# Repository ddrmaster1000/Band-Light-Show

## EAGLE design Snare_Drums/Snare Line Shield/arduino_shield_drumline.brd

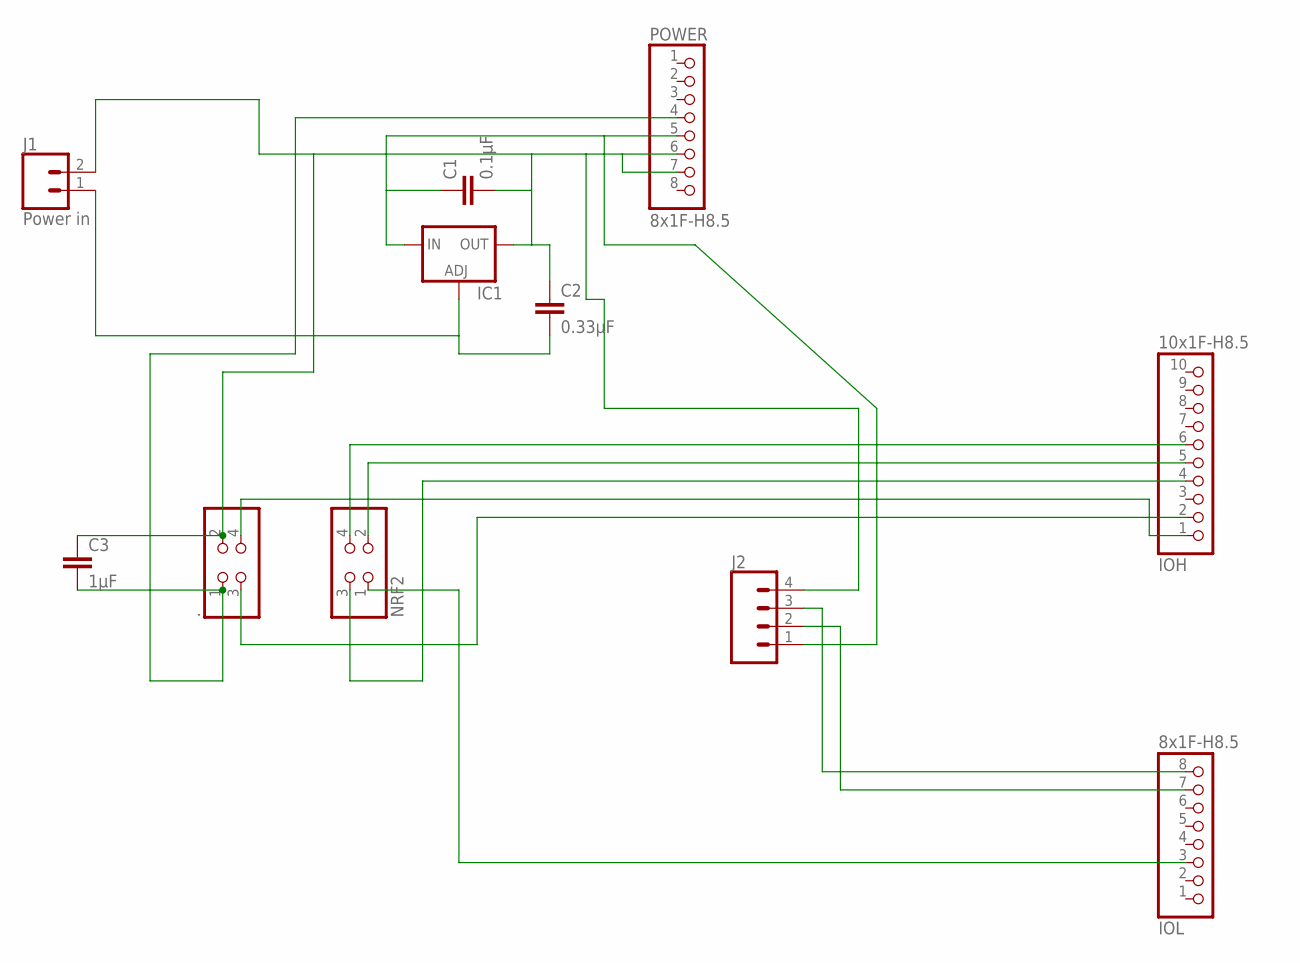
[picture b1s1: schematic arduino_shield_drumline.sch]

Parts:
.: PINHD-2X2; 2X02
C1: 0.1µF; 0805
C2: 0.33µF; 0805
C3: 1µF; 0805
IC1: LM138-TS; TO220S
IOH: 10x1F-H8.5; 1X10
IOL: 8x1F-H8.5; 1X08
J1: Power in; 1X02
J2: CONN_04; 1X04
NRF2: PINHD-2X2; 2X02
POWER: 8x1F-H8.5; 1X08

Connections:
GND: ..2, C1.2, C2.1, C3.1, IC1.2 (OUT), J1.2, J2.4, POWER.6, POWER.7
unnamed: ..1, C3.2, POWER.4
unnamed: IOH.5, NRF2.2
unnamed: ..4, IOH.1
unnamed: ..3, IOH.2
unnamed: IOH.6, NRF2.4
unnamed: IOL.3, NRF2.1
unnamed: IOH.4, NRF2.3
unnamed: C1.1, IC1.3 (IN), J2.1, POWER.5
unnamed: C2.2, IC1.1 (ADJ), J1.1
unnamed: IOL.8, J2.3
unnamed: IOL.7, J2.2

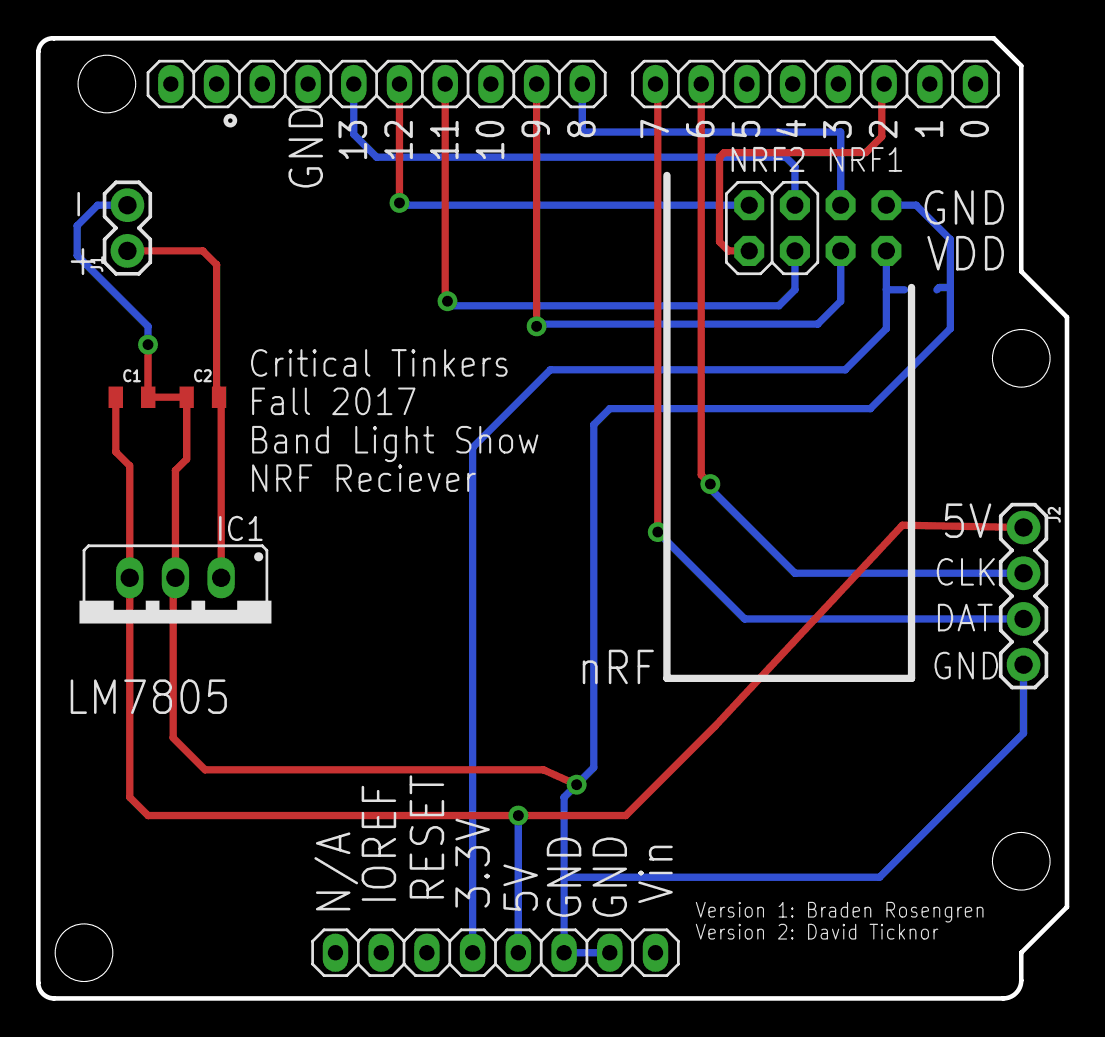
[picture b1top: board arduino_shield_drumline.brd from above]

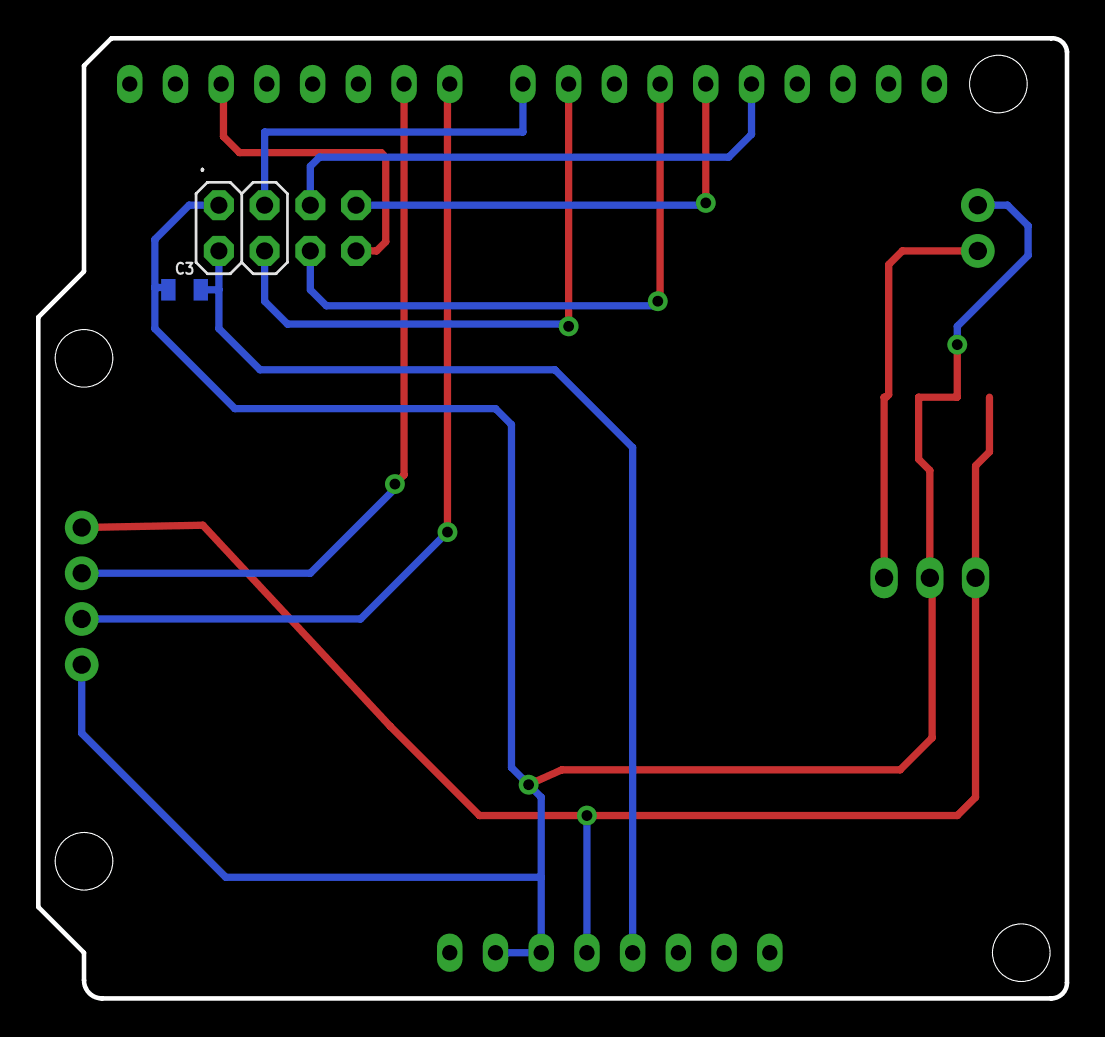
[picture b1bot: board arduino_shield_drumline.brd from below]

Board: 2 copper layers, 57.2 x 53.3 mm, 11 parts (2 on the bottom side), 12 nets.

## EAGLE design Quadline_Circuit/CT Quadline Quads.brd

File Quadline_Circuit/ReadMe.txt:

The Quadline was made such that it was the bassline diagram copied 4x with the GND and 12V connected accordingly. 
Thus there is no schematic, it will say there is an error but this is not an issue.
Developed on EAGLE 8.3.1

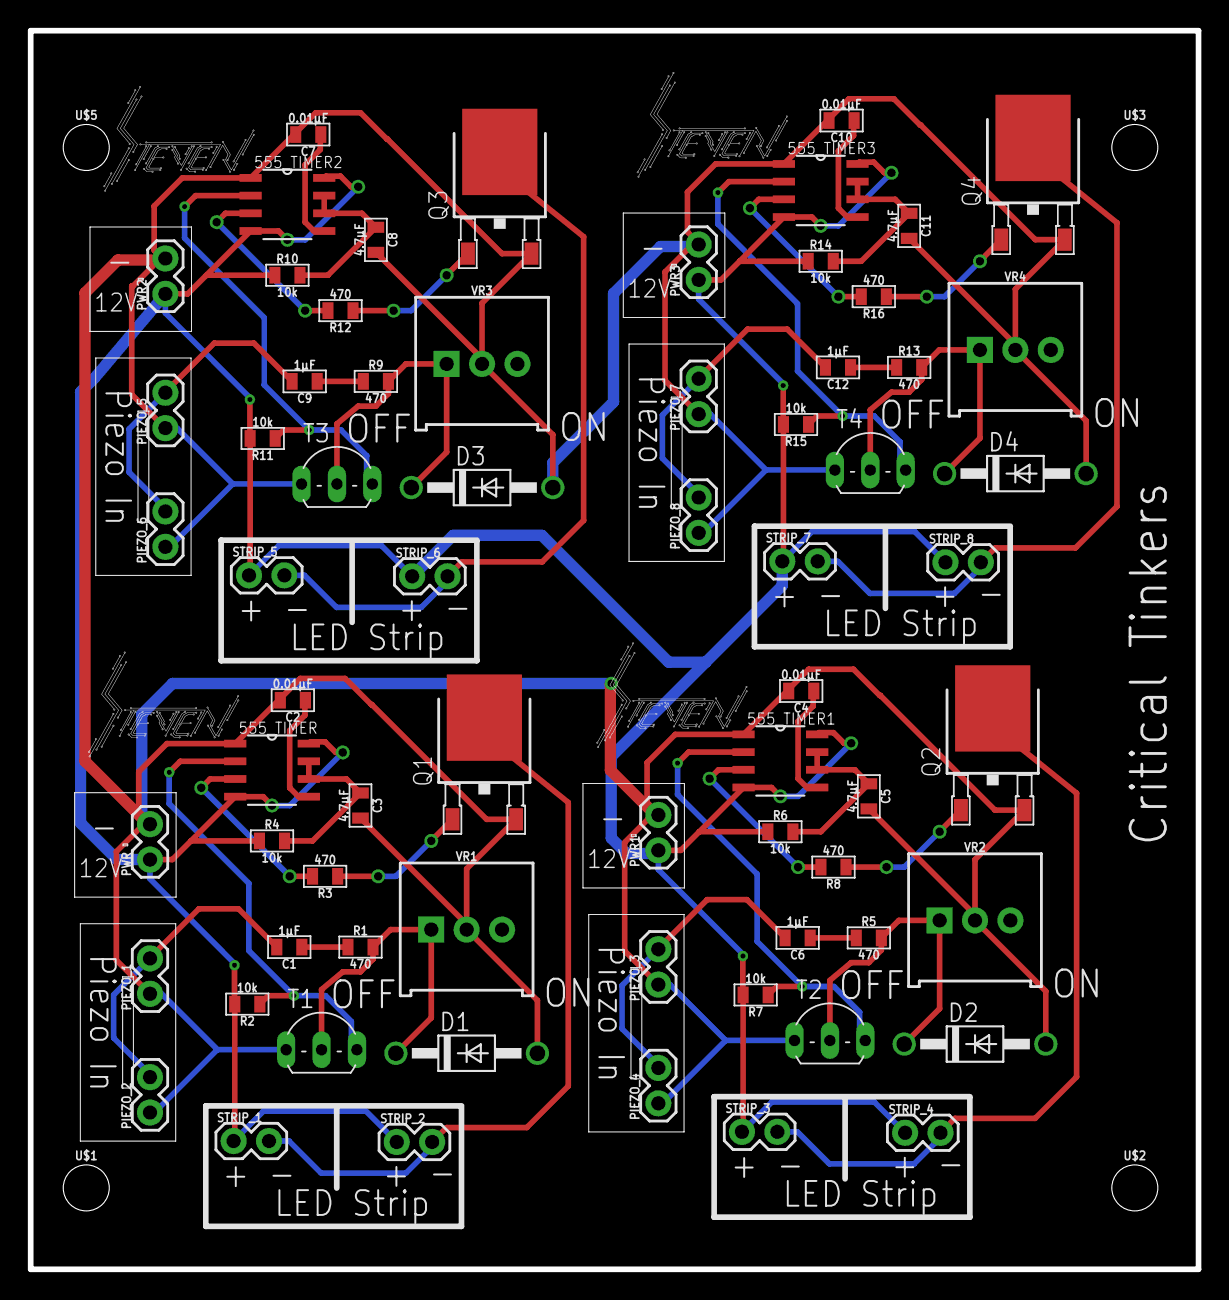
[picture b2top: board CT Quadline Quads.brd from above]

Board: 2 copper layers, 83.8 x 88.9 mm, 72 parts (0 on the bottom side), 38 nets.

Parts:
555_TIMER, 555_TIMER1, 555_TIMER2, 555_TIMER3: LM555CM; SOIC127P600X175-8N
C1, C6, C9, C12: 1µF; 0805
C2, C4, C7, C10: 0.01µF; 0805
C3, C5, C8, C11: 4.7µF; 0805
D1, D2, D3, D4: 1N4006; DO41-10
PIEZO_1, PIEZO_2, PIEZO_3, PIEZO_4, PIEZO_5, PIEZO_6, PIEZO_7, PIEZO_8: 1X02
PWR, PWR1, PWR2, PWR3: 1X02
Q1, Q2, Q3, Q4: RFD14N05SM9A; TO252
R1, R3, R5, R8, R9, R12, R13, R16: 470; 0805
R2, R4, R6, R7, R10, R11, R14, R15: 10k; 0805
STRIP_1, STRIP_2, STRIP_3, STRIP_4, STRIP_5, STRIP_6, STRIP_7, STRIP_8: 1X02
T1, T2, T3, T4: 2N2222; TO92-EBC-OVAL
U$1, U$2, U$3, U$5: STAND-OFF
VR1, VR2, VR3, VR4: 10k; TRIMPOT-PTH-3386U

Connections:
12V: 555_TIMER.4, 555_TIMER.8, 555_TIMER1.4, 555_TIMER1.8, 555_TIMER2.4, 555_TIMER2.8, 555_TIMER3.4, 555_TIMER3.8, PWR.1, PWR1.1, PWR2.1, PWR3.1, R2.2, R4.1, R6.1, R7.2, R10.1, R11.2, R14.1, R15.2, STRIP_1.1, STRIP_2.1, STRIP_3.1, STRIP_4.1, STRIP_5.1, STRIP_6.1, STRIP_7.1, STRIP_8.1
GATE: Q1.1, R3.1
GATE1: Q2.1, R8.1
GATE2: Q3.1, R12.1
GATE3: Q4.1, R16.1
GND: 555_TIMER.1, 555_TIMER1.1, 555_TIMER2.1, 555_TIMER3.1, C2.2, C3.2, C4.2, C5.2, C7.2, C8.2, C10.2, C11.2, D1.A, D2.A, D3.A, D4.A, PIEZO_1.1, PIEZO_2.1, PIEZO_3.1, PIEZO_4.1, PIEZO_5.1, PIEZO_6.1, PIEZO_7.1, PIEZO_8.1, PWR.2, PWR1.2, PWR2.2, PWR3.2, Q1.2, Q2.2, Q3.2, Q4.2, T1.E, T2.E, T3.E, T4.E, VR1.2, VR2.2, VR3.2, VR4.2
unnamed: C1.1, R1.1
unnamed: C6.2, PIEZO_3.2, PIEZO_4.2
unnamed: 555_TIMER.3, R3.2
unnamed: 555_TIMER.5, C2.1
unnamed: C1.2, PIEZO_1.2, PIEZO_2.2
unnamed: 555_TIMER1.5, C4.1
unnamed: 555_TIMER1.6, 555_TIMER1.7, C5.1, R6.2
unnamed: 555_TIMER.6, 555_TIMER.7, C3.1, R4.2
unnamed: C6.1, R5.1
unnamed: 555_TIMER1.3, R8.2
unnamed: C9.2, PIEZO_5.2, PIEZO_6.2
unnamed: 555_TIMER2.5, C7.1
unnamed: 555_TIMER2.6, 555_TIMER2.7, C8.1, R10.2
unnamed: C9.1, R9.1
unnamed: 555_TIMER2.3, R12.2
unnamed: C12.2, PIEZO_7.2, PIEZO_8.2
unnamed: 555_TIMER3.5, C10.1
unnamed: 555_TIMER3.6, 555_TIMER3.7, C11.1, R14.2
unnamed: C12.1, R13.1
unnamed: 555_TIMER3.3, R16.2
NO_CONNECT_TO_TRIGGER: D1.C, R1.2, T1.B, VR1.1
NO_CONNECT_TO_TRIGGER1: D2.C, R5.2, T2.B, VR2.1
NO_CONNECT_TO_TRIGGER2: D3.C, R9.2, T3.B, VR3.1
NO_CONNECT_TO_TRIGGER3: D4.C, R13.2, T4.B, VR4.1
STRIP_GND_0: Q1.3, STRIP_1.2, STRIP_2.2
STRIP_GND_1: Q2.3, STRIP_3.2, STRIP_4.2
STRIP_GND_2: Q3.3, STRIP_5.2, STRIP_6.2
STRIP_GND_3: Q4.3, STRIP_7.2, STRIP_8.2
TRIGGER: 555_TIMER.2, R2.1, T1.C
TRIGGER1: 555_TIMER1.2, R7.1, T2.C
TRIGGER2: 555_TIMER2.2, R11.1, T3.C
TRIGGER3: 555_TIMER3.2, R15.1, T4.C

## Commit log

2018-03-01 First Upload
    Includes Bass Drum and Quad Drum Eagle files + STL files for enclosures. Does not include the Snare drum code, hardware, or parts list at this time. use parts list as a guide, it is not perfect.
2018-03-01 Snare Line Code
    Added Snare Line code from David & Steve
2018-03-31 EE 333 Notes
    Uploaded a base schematic, parts, and info

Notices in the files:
parts and their libraries:
SparkFun-Capacitors: Licensing: Creative Commons ShareAlike 4.0 International - https://creativecommons.org/licenses/by-sa/4.0
